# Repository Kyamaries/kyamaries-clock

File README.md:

# kyamaries-clock
 My first HPS clock.

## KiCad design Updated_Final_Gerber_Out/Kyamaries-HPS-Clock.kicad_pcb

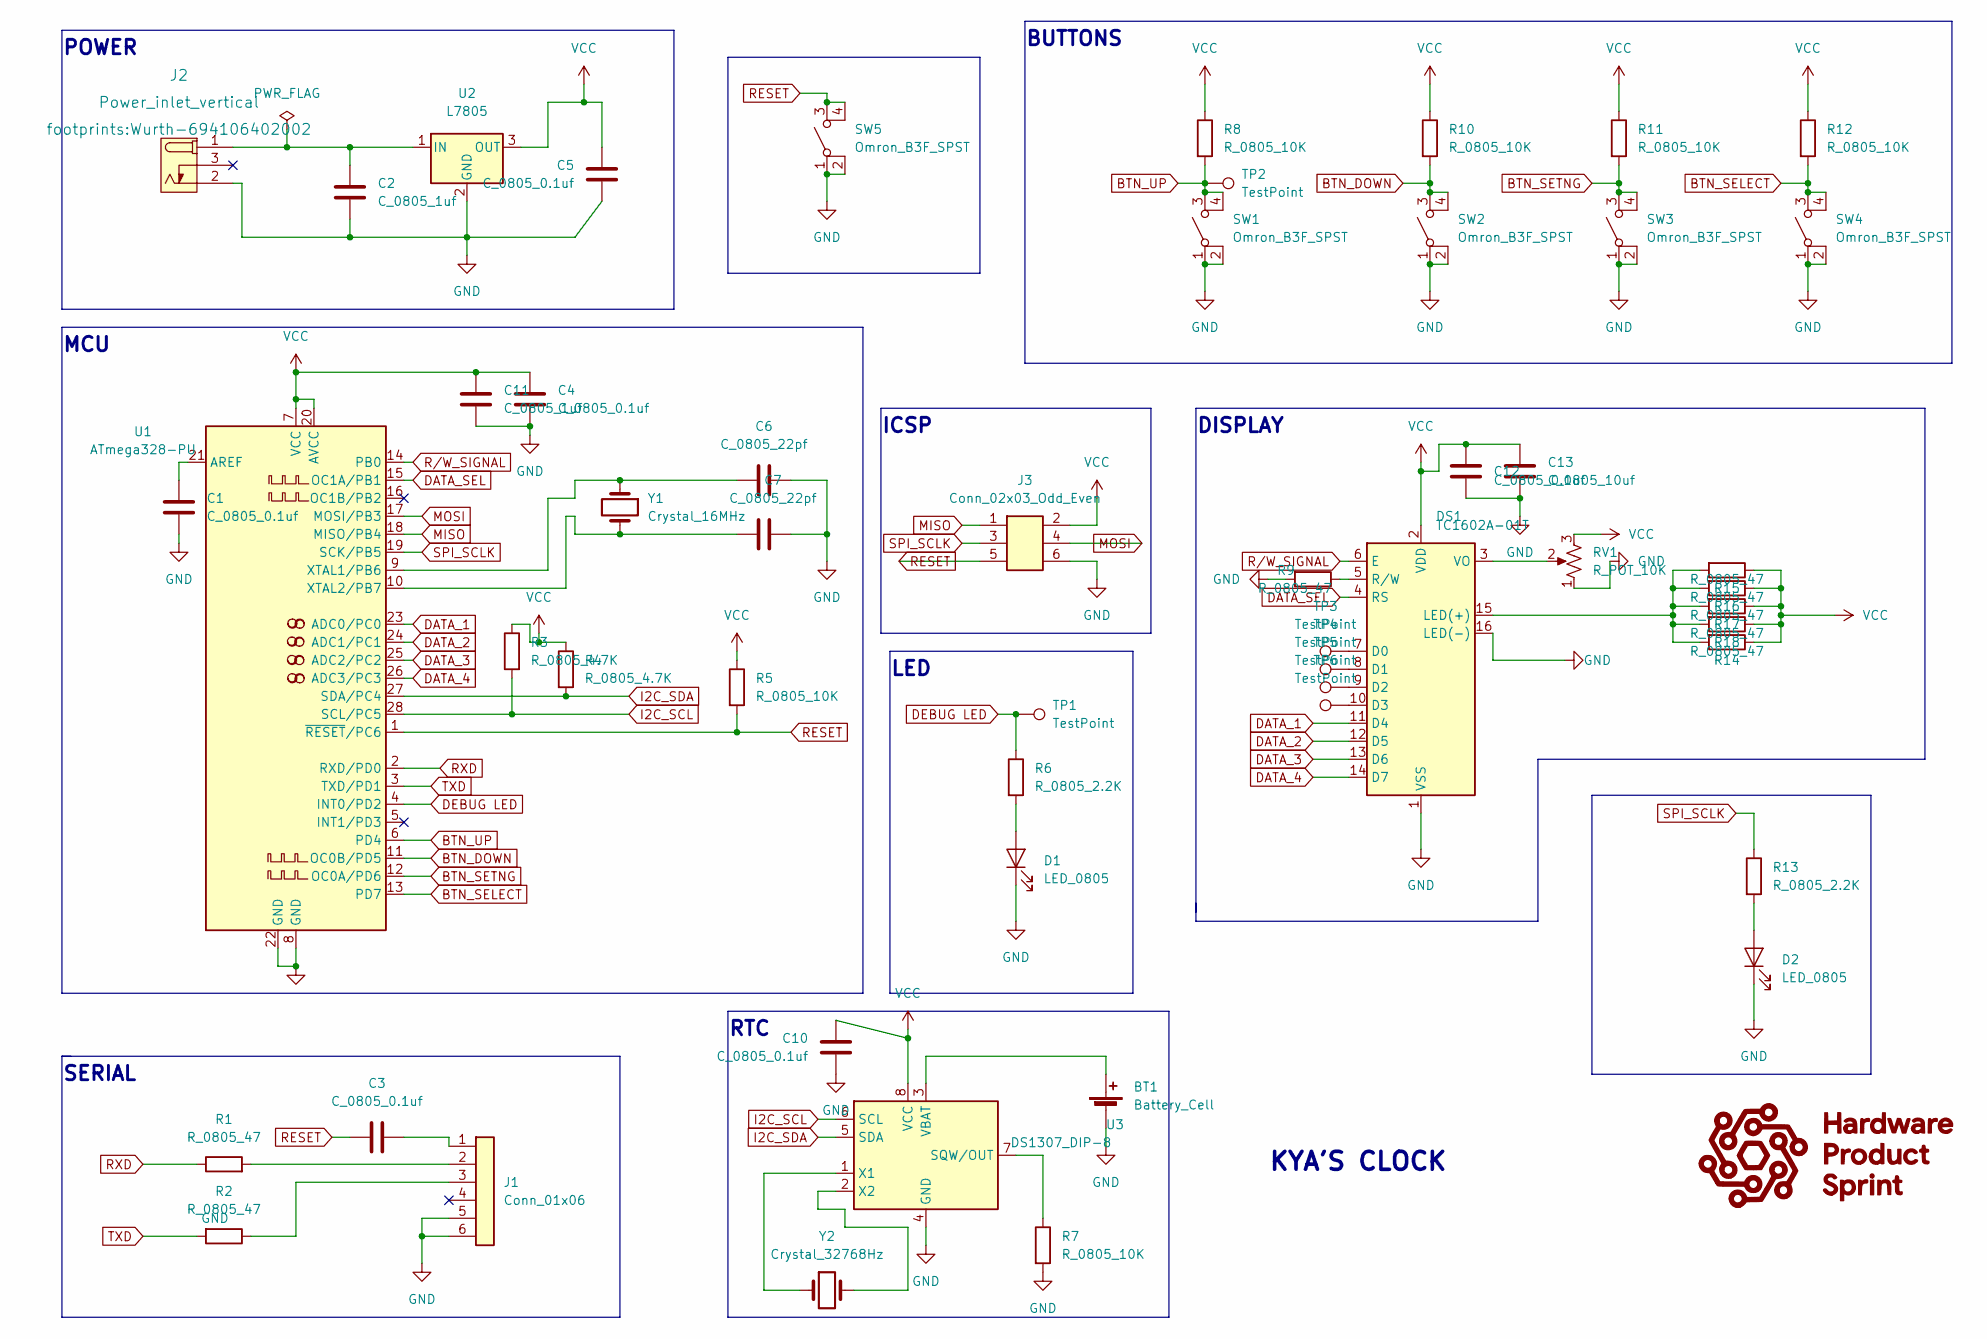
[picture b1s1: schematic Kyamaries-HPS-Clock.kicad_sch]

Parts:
BT1: Battery_Cell; BatteryHolder_Keystone_106_1x20mm; MPN BS-7; Digikey PN BS-7-ND
C1, C3, C4, C5, C10, C12: C_0805_0.1uf; C_0805_2012Metric; Voltage N/A; Tolerance N/A; MPN 08055C104KAT2A; Digikey PN 478-1395-1-ND
C2, C11: C_0805_1uf; C_0805_2012Metric; Voltage N/A; Tolerance N/A; MPN CC0805KKX7R8BB105; Digikey PN 311-1456-1-ND
C6, C7: C_0805_22pf; C_0805_2012Metric; Voltage N/A; Tolerance N/A; MPN CC0805JRNPO9BN220; Digikey PN 311-1103-1-ND
C13: C_0805_10uf; C_0805_2012Metric; Voltage N/A; Tolerance N/A; MPN GRM21BR61E106KA73L; Digikey PN 490-5523-1-ND
D1, D2: LED_0805; LED_0805_2012Metric; MPN 150080RS75000; Digikey PN 732-4984-1-ND
DS1: TC1602A-01T; MPN 1447; Digikey PN 1528-2212-ND
J1: Conn_01x06; PinHeader_1x06_P2.54mm_Vertical; MPN 61300611121; Digikey PN 732-5319-ND
J2: Power_inlet_vertical; Wurth-694106402002; MPN 694106402002; Digikey PN 732-5931-ND
J3: Conn_02x03_Odd_Even; PinHeader_2x03_P2.54mm_Vertical; MPN PRPC003DAAN-RC; Digikey PN S2011EC-03-ND
R1, R2, R9, R14, R15, R16, R17, R18: R_0805_47; R_0805_2012Metric; Tolerance N/A; Mouser PN N/A; Digikey PN RC0805FR-0747RL
R3, R4: R_0805_4.7K; R_0805_2012Metric; Tolerance N/A; MPN RC0805FR-074K7L; Digikey PN 311-4.70KCRCT-ND
R5, R7, R8, R10, R11, R12: R_0805_10K; R_0805_2012Metric; Tolerance N/A; MPN RC0805FR-0710KL; Digikey PN 311-10.0KCRCT-ND
R6, R13: R_0805_2.2K; R_0805_2012Metric; Tolerance N/A; MPN N/A; Digikey PN 311-2.20KCRCT-ND
RV1: R_POT_10K; Potentiometer_Bourns_3386P_Vertical; MPN 3386P-1-103TLF; Digikey PN 3386P-103TLF-ND
SW1, SW2, SW3, SW4, SW5: Omron_B3F_SPST; SW_SPST_Omron_B3FS-100xP; MPN B3FS-1000P; Digikey PN SW423CT-ND
TP1, TP2, TP3, TP4, TP5, TP6: TestPoint; TestPoint_THTPad_D2.0mm_Drill1.0mm
U1: ATmega328-PU; DIP-28_W7.62mm; MPN ED281DT; Digikey PN ED3050-5-ND
U2: L7805; TO-252-2; MPN L7805CDT-TR; Digikey PN 497-7255-1-ND
U3: DS1307_DIP-8; DIP-8_W7.62mm; MPN A 08-LC-TT; Digikey PN AE9986-ND
Y1: Crystal_16MHz; Crystal_SMD_HC49-SD; MPN ECS-160-20-5PXDN-TR; Digikey PN XC1299CT-ND
Y2: Crystal_32768Hz; Crystal_SMD_2Pin_3.2x1.5mm; MPN Q 0,032768-JTX310-12,5-20-T1-HMR-50K-LF; Digikey PN 1908-1314-1-ND

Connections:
BTN_DOWN: R10.2, SW2.3 (B), SW2.4 (B), U1.11 (OC0B/PD5)
BTN_SELECT: R12.2, SW4.3 (B), SW4.4 (B), U1.13 (PD7)
BTN_SETNG: R11.2, SW3.3 (B), SW3.4 (B), U1.12 (OC0A/PD6)
BTN_UP: R8.2, SW1.3 (B), SW1.4 (B), TP2.1, U1.6 (PD4)
DATA_1: DS1.11 (D4), U1.23 (ADC0/PC0)
DATA_2: DS1.12 (D5), U1.24 (ADC1/PC1)
DATA_3: DS1.13 (D6), U1.25 (ADC2/PC2)
DATA_4: DS1.14 (D7), U1.26 (ADC3/PC3)
DATA_SEL: DS1.4 (RS), U1.15 (OC1A/PB1)
DEBUG LED: R6.1, TP1.1, U1.4 (INT0/PD2)
GND: BT1.2 (-), C1.2, C2.2, C4.2, C5.1, C6.2, C7.2, C10.1, C11.2, C12.2, C13.2, D1.1 (K), D2.1 (K), DS1.1 (VSS), DS1.16 (LED(-)), J1.5, J1.6, J2.2 (OUT), J3.6, R7.2, R9.2, RV1.1, SW1.1 (A), SW1.2 (A), SW2.1 (A), SW2.2 (A), SW3.1 (A), SW3.2 (A), SW4.1 (A), SW4.2 (A), SW5.1 (A), SW5.2 (A), U1.8 (GND), U1.22 (GND), U2.2 (GND), U3.4 (GND)
I2C_SCL: R3.2, U1.28 (SCL/PC5), U3.6 (SCL)
I2C_SDA: R4.2, U1.27 (SDA/PC4), U3.5 (SDA)
MISO: J3.1, U1.18 (MISO/PB4)
MOSI: J3.4, U1.17 (MOSI/PB3)
unnamed: BT1.1 (+), U3.3 (VBAT)
unnamed: C1.1, U1.21 (AREF)
unnamed: C2.1, J2.1 (POLE), U2.1 (IN)
unnamed: C3.1, J1.1
unnamed: C6.1, U1.9 (XTAL1/PB6), Y1.1
unnamed: C7.1, U1.10 (XTAL2/PB7), Y1.2
unnamed: D1.2 (A), R6.2
unnamed: D2.2 (A), R13.2
unnamed: DS1.3 (VO), RV1.2
unnamed: DS1.5 (R/W), R9.1
unnamed: DS1.7 (D0), TP3.1
unnamed: DS1.8 (D1), TP4.1
unnamed: DS1.9 (D2), TP5.1
unnamed: DS1.10 (D3), TP6.1
unnamed: DS1.15 (LED(+)), R14.2, R15.2, R16.2, R17.2, R18.2
unnamed: J1.2, R1.2
unnamed: J1.3, R2.1
unnamed: R7.1, U3.7 (SQW/OUT)
unnamed 33: U3.1 (X1), Y2.1; also elsewhere on the board
unnamed 34: U3.2 (X2), Y2.2; also elsewhere on the board
RESET: C3.2, J3.5, R5.2, SW5.3 (B), SW5.4 (B), U1.1 (~RESET/PC6)
RXD: R1.1, U1.2 (RXD/PD0)
R/W_SIGNAL: DS1.6 (E), U1.14 (PB0)
SPI_SCLK: J3.3, R13.1, U1.19 (SCK/PB5)
TXD: R2.2, U1.3 (TXD/PD1)
VCC: C4.1, C5.2, C10.2, C11.1, C12.1, C13.1, DS1.2 (VDD), J3.2, R3.1, R4.1, R5.1, R8.1, R10.1, R11.1, R12.1, R14.1, R15.1, R16.1, R17.1, R18.1, RV1.3, U1.7 (VCC), U1.20 (AVCC), U2.3 (OUT), U3.8 (VCC)

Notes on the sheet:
BUTTONS
LED
RTC
SERIAL
ICSP
MCU
KYA'S CLOCK
DISPLAY
POWER

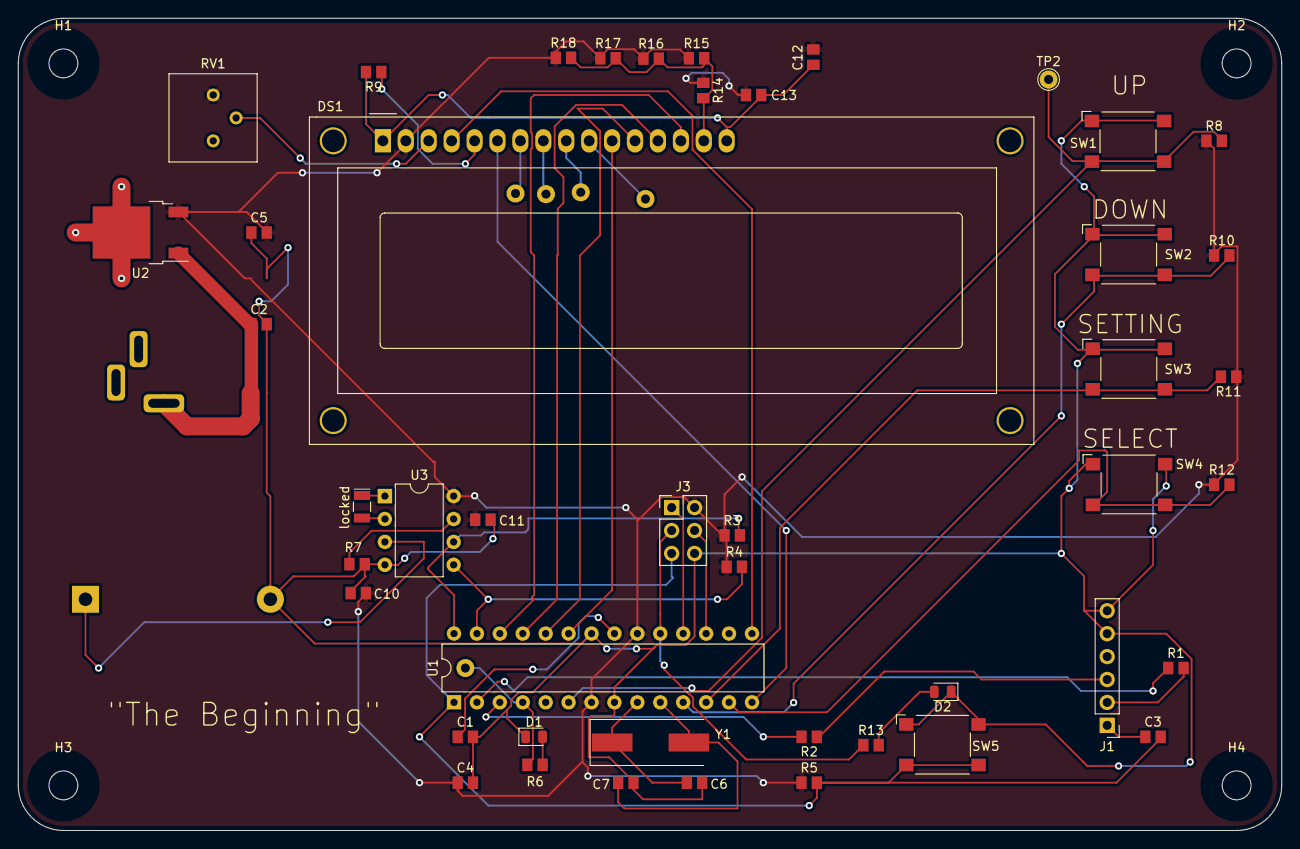
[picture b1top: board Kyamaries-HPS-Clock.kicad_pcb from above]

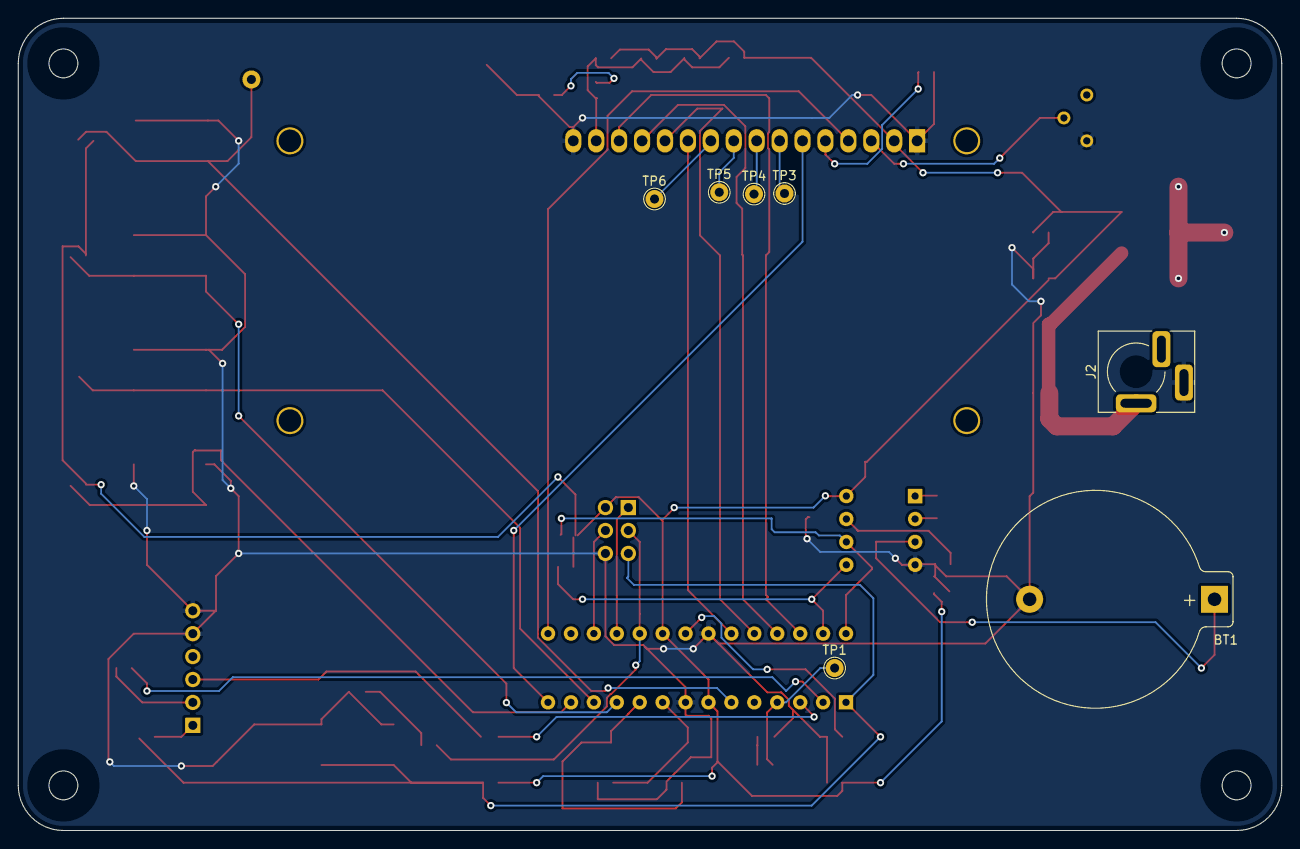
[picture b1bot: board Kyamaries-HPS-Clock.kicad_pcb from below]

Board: 2 copper layers, 140.0 x 90.0 mm, 57 parts (7 on the bottom side), 41 nets.

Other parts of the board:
H1, H2, H3, H4: MountingHole; MountingHole_3.2mm_M3
locked: Crystal_32768Hz; Crystal_SMD_2Pin_3.2x1.5mm

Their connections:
unnamed 33: locked.1; also elsewhere on the board
unnamed 34: locked.2; also elsewhere on the board

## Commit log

2022-06-12 HPS-clock-kicad
2022-07-19 checkpoint
2022-07-21 Schematic_Update
2022-07-22 FINAL_GERBER_OUT
2022-07-22 Updated schematics
2022-07-22 .kicad_pro file update
2022-07-23 Updated final Gerber
